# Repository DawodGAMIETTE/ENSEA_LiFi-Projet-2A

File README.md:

# Indoor communication via Li-Fi - Project 2nd year 2023/24
Use Li-Fi (Light Fidelity) technology to establish wireless communication between a transmitter equipped with LEDs and a photosensitive receiver.
Unlike infrared technologies, which are subject to interference, our application uses visible light to transmit data quickly and efficiently.

## Equipment used
- 2 Arduino Nano 33 IoT boards
- an electronic board equipped with 6 LEDs (sender)
- an electronic board equipped with a photosensitive sensor (receiver)

## Git repository description
In this Git repository you will find :
- the KiCad files for the PCB used to receive the light signals,
- the codes to be implemented on the Arduino boards in order to send, receive and process the light signals.

## Students in charge of the project
- GAMIETTE David

## Teachers supervising the project
- DUMAS Jean-Michel

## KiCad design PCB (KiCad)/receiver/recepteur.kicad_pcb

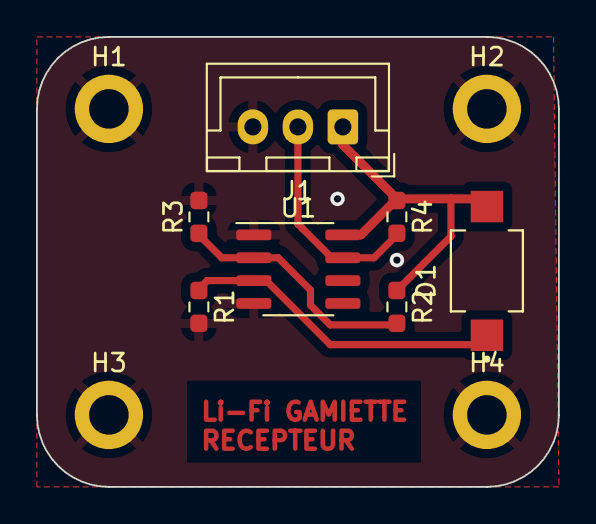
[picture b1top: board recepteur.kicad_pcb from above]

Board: 2 copper layers, 29.0 x 25.0 mm, 11 parts (0 on the bottom side), 5 nets.

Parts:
D1: VBPW34SR; DIO_VBPW34SR
H1, H2, H3, H4: MountingHole_Pad; MountingHole_2.2mm_M2_DIN965_Pad
J1: Conn_01x03_Pin; JST_XH_B3B-XH-A_1x03_P2.50mm_Vertical
R1: 220k; R_0603_1608Metric_Pad0.98x0.95mm_HandSolder
R2: 1k; R_0603_1608Metric_Pad0.98x0.95mm_HandSolder
R3: 180; R_0603_1608Metric_Pad0.98x0.95mm_HandSolder
R4: 10k; R_0603_1608Metric_Pad0.98x0.95mm_HandSolder
U1: LM311; SOIC-8_3.9x4.9mm_P1.27mm

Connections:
+5V: D1.A, J1.1, R2.1, R4.1, U1.8 (V+)
GND: H1.1, H2.1, H3.1, H4.1, J1.3, R1.2, R3.2, U1.1 (GND), U1.4 (V-)
unnamed: J1.2, R4.2, U1.7
unnamed: R2.2, R3.1, U1.2 (+)
unnamed: D1.C, R1.1, U1.3 (-)

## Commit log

2024-10-19 add reader
2024-10-19 add receiver
2024-10-19 add sender
2024-10-19 add footprint-to-import
